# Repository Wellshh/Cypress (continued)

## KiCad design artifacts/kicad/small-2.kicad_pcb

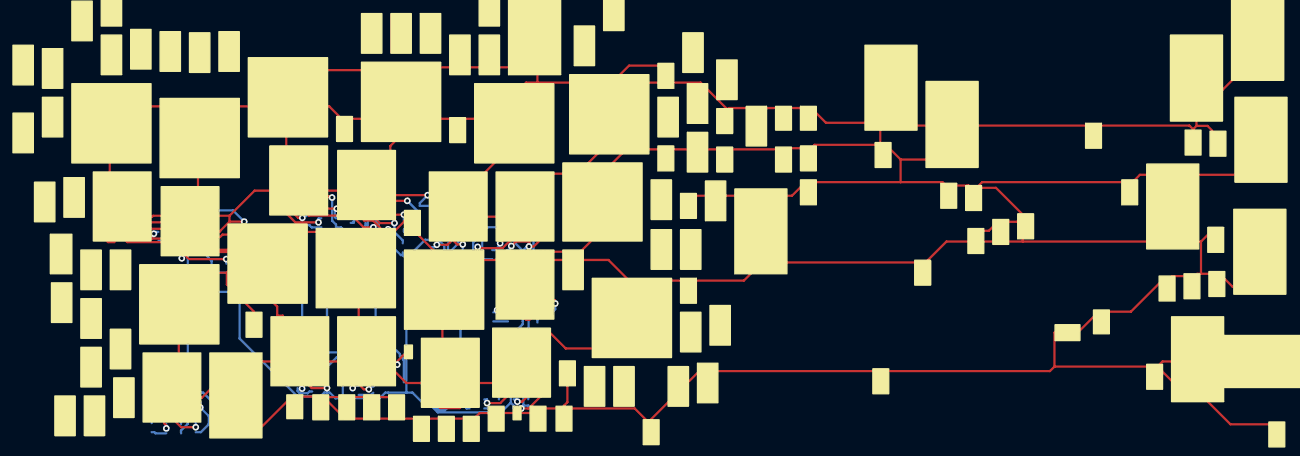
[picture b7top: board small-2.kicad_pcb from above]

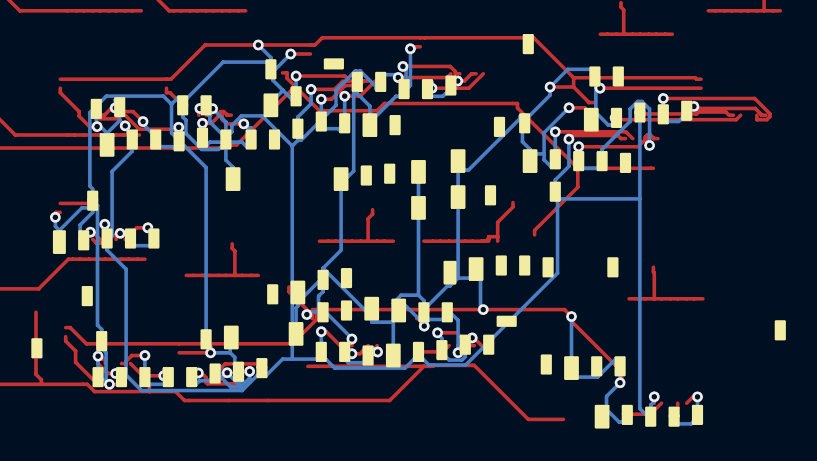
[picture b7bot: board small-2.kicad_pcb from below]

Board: 2 copper layers, 240 parts (106 on the bottom side), 87 nets.

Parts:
C1_1_4: C1_1_4
C1_2_4: C1_2_4
C1_3_4: C1_3_4
C1_4_4: C1_4_4
C1_5_4: C1_5_4
C1_6_4: C1_6_4
C1_7_4: C1_7_4
C1_8_4: C1_8_4
C1_9_4: C1_9_4
C1_10_4: C1_10_4
C1_11_4: C1_11_4
C1_12_4: C1_12_4
C2_1_4: C2_1_4
C2_2_4: C2_2_4
C2_3_4: C2_3_4
C2_4_4: C2_4_4
C2_5_4: C2_5_4
C2_6_4: C2_6_4
C2_7_4: C2_7_4
C2_8_4: C2_8_4
C2_9_4: C2_9_4
C2_10_4: C2_10_4
C2_11_4: C2_11_4
C2_12_4: C2_12_4
C3_1_4: C3_1_4
C3_2_4: C3_2_4
C3_3_4: C3_3_4
C3_4_4: C3_4_4
C3_5_4: C3_5_4
C3_6_4: C3_6_4
C3_7_4: C3_7_4
C3_8_4: C3_8_4
C3_9_4: C3_9_4
C3_10_4: C3_10_4
C3_11_4: C3_11_4
C3_12_4: C3_12_4
C4_1_4: C4_1_4
C4_2_4: C4_2_4
C4_3_4: C4_3_4
C4_4_4: C4_4_4
C4_5_4: C4_5_4
C4_6_4: C4_6_4
C4_7_4: C4_7_4
C4_8_4: C4_8_4
C4_9_4: C4_9_4
C4_10_4: C4_10_4
C4_11_4: C4_11_4
C4_12_4: C4_12_4
C5_1_4: C5_1_4
C5_2_4: C5_2_4
C5_3_4: C5_3_4
C5_4_4: C5_4_4
C5_5_4: C5_5_4
C5_6_4: C5_6_4
C5_7_4: C5_7_4
C5_8_4: C5_8_4
C5_9_4: C5_9_4
C5_10_4: C5_10_4
C5_11_4: C5_11_4
C5_12_4: C5_12_4
C6_1_4: C6_1_4
C6_2_4: C6_2_4
C6_3_4: C6_3_4
C6_4_4: C6_4_4
C6_5_4: C6_5_4
C6_6_4: C6_6_4
C6_7_4: C6_7_4
C6_8_4: C6_8_4
C6_9_4: C6_9_4
C6_10_4: C6_10_4
C6_11_4: C6_11_4
C6_12_4: C6_12_4
C7_1_4: C7_1_4
C7_2_4: C7_2_4
C7_3_4: C7_3_4
C7_4_4: C7_4_4
C7_5_4: C7_5_4
C7_6_4: C7_6_4
C7_7_4: C7_7_4
C7_8_4: C7_8_4
C7_9_4: C7_9_4
C7_10_4: C7_10_4
C7_11_4: C7_11_4
C7_12_4: C7_12_4
C8_1_4: C8_1_4
C8_2_4: C8_2_4
C8_3_4: C8_3_4
C8_4_4: C8_4_4
C8_5_4: C8_5_4
C8_6_4: C8_6_4
C8_7_4: C8_7_4
C8_8_4: C8_8_4
C8_9_4: C8_9_4
C8_10_4: C8_10_4
C8_11_4: C8_11_4
C8_12_4: C8_12_4
C10_1_4: C10_1_4
C10_2_4: C10_2_4
C10_3_4: C10_3_4
C10_4_4: C10_4_4
C10_5_4: C10_5_4
C10_6_4: C10_6_4
C10_7_4: C10_7_4
C10_8_4: C10_8_4
C10_9_4: C10_9_4
C10_10_4: C10_10_4
C10_11_4: C10_11_4
C10_12_4: C10_12_4
C11_1_4: C11_1_4
C11_2_4: C11_2_4
C11_3_4: C11_3_4
C11_4_4: C11_4_4
C11_5_4: C11_5_4
C11_6_4: C11_6_4
C11_7_4: C11_7_4
C11_8_4: C11_8_4
C11_9_4: C11_9_4
C11_10_4: C11_10_4
C11_11_4: C11_11_4
C11_12_4: C11_12_4
C12_1_4: C12_1_4
C12_2_4: C12_2_4
C12_3_4: C12_3_4
C12_4_4: C12_4_4
C12_5_4: C12_5_4
C12_6_4: C12_6_4
C12_7_4: C12_7_4
C12_8_4: C12_8_4
C12_9_4: C12_9_4
C12_10_4: C12_10_4
C12_11_4: C12_11_4
C12_12_4: C12_12_4
C13_1_4: C13_1_4
C13_2_4: C13_2_4
C13_3_4: C13_3_4
C13_4_4: C13_4_4
C13_5_4: C13_5_4
C13_6_4: C13_6_4
C13_7_4: C13_7_4
C13_8_4: C13_8_4
C13_9_4: C13_9_4
C13_10_4: C13_10_4
C13_11_4: C13_11_4
C13_12_4: C13_12_4
C14_1_4: C14_1_4
C14_2_4: C14_2_4
C14_3_4: C14_3_4
C14_4_4: C14_4_4
C14_5_4: C14_5_4
C14_6_4: C14_6_4
C14_7_4: C14_7_4
C14_8_4: C14_8_4
C14_9_4: C14_9_4
C14_10_4: C14_10_4
C14_11_4: C14_11_4
C14_12_4: C14_12_4
C15_1_4: C15_1_4
C15_2_4: C15_2_4
C15_3_4: C15_3_4
C15_4_4: C15_4_4
C15_5_4: C15_5_4
C15_6_4: C15_6_4
C15_7_4: C15_7_4
C15_8_4: C15_8_4
C15_9_4: C15_9_4
C15_10_4: C15_10_4
C15_11_4: C15_11_4
C15_12_4: C15_12_4
L1_1_4: L1_1_4
L1_2_4: L1_2_4
L1_3_4: L1_3_4
L1_4_4: L1_4_4
L1_5_4: L1_5_4
L1_6_4: L1_6_4
L1_7_4: L1_7_4
L1_8_4: L1_8_4
L1_9_4: L1_9_4
L1_10_4: L1_10_4
L1_11_4: L1_11_4
L1_12_4: L1_12_4
R1_1_4: R1_1_4
R1_2_4: R1_2_4
R1_3_4: R1_3_4
R1_4_4: R1_4_4
R1_5_4: R1_5_4
R1_6_4: R1_6_4
R1_7_4: R1_7_4
R1_8_4: R1_8_4
R1_9_4: R1_9_4
R1_10_4: R1_10_4
R1_11_4: R1_11_4
R1_12_4: R1_12_4
R2_1_4: R2_1_4
R2_2_4: R2_2_4
R2_3_4: R2_3_4
R2_4_4: R2_4_4
R2_5_4: R2_5_4
R2_6_4: R2_6_4
R2_7_4: R2_7_4
R2_8_4: R2_8_4
R2_9_4: R2_9_4
R2_10_4: R2_10_4
R2_11_4: R2_11_4
R2_12_4: R2_12_4
R3_1_4: R3_1_4
R3_2_4: R3_2_4
R3_3_4: R3_3_4
R3_4_4: R3_4_4
R3_5_4: R3_5_4
R3_6_4: R3_6_4
R3_7_4: R3_7_4
R3_8_4: R3_8_4
R3_9_4: R3_9_4
R3_10_4: R3_10_4
R3_11_4: R3_11_4
R3_12_4: R3_12_4
R4_1_4: R4_1_4
R4_2_4: R4_2_4
R4_3_4: R4_3_4
R4_4_4: R4_4_4
R4_5_4: R4_5_4
R4_6_4: R4_6_4
R4_7_4: R4_7_4
R4_8_4: R4_8_4
R4_9_4: R4_9_4
R4_10_4: R4_10_4
R4_11_4: R4_11_4
R4_12_4: R4_12_4
U1_1_4: U1_1_4
U1_2_4: U1_2_4
U1_3_4: U1_3_4
U1_4_4: U1_4_4
U1_5_4: U1_5_4
U1_6_4: U1_6_4
U1_7_4: U1_7_4
U1_8_4: U1_8_4
U1_9_4: U1_9_4
U1_10_4: U1_10_4
U1_11_4: U1_11_4
U1_12_4: U1_12_4

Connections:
AG_PH_BOOTRC_24: C11_1_4.0, R4_1_4.0
AG_PH_BOOTRC_25: C11_2_4.0, R4_2_4.0
AG_PH_BOOTRC_26: C11_3_4.0, R4_3_4.0
AG_PH_BOOTRC_27: C11_4_4.0, R4_4_4.0
AG_PH_BOOTRC_28: C11_5_4.0, R4_5_4.0
AG_PH_BOOTRC_29: C11_6_4.0, R4_6_4.0
AG_PH_BOOTRC_30: C11_7_4.0, R4_7_4.0
AG_PH_BOOTRC_31: C11_8_4.0, R4_8_4.0
AG_PH_BOOTRC_32: C11_9_4.0, R4_9_4.0
AG_PH_BOOTRC_33: C11_11_4.0, R4_11_4.0
AG_PH_BOOTRC_34: C11_10_4.0, R4_10_4.0
AG_PH_BOOTRC_35: C11_12_4.0, R4_12_4.0
AG_PH_BOOT_24: R4_1_4.1, U1_1_4.2
AG_PH_BOOT_25: R4_2_4.1, U1_2_4.2
AG_PH_BOOT_26: R4_3_4.1, U1_3_4.2
AG_PH_BOOT_27: R4_4_4.1, U1_4_4.2
AG_PH_BOOT_28: R4_5_4.1, U1_5_4.2
AG_PH_BOOT_29: R4_6_4.1, U1_6_4.2
AG_PH_BOOT_30: R4_7_4.1, U1_7_4.2
AG_PH_BOOT_31: R4_8_4.1, U1_8_4.2
AG_PH_BOOT_32: R4_9_4.1, U1_9_4.2
AG_PH_BOOT_33: R4_11_4.1, U1_11_4.2
AG_PH_BOOT_34: R4_10_4.1, U1_10_4.2
AG_PH_BOOT_35: R4_12_4.1, U1_12_4.2
AG_PH_PHASE_24: C11_1_4.1, U1_1_4.3
AG_PH_PHASE_25: C11_2_4.1, U1_2_4.3
AG_PH_PHASE_26: C11_3_4.1, U1_3_4.3
AG_PH_PHASE_27: C11_4_4.1, U1_4_4.3
AG_PH_PHASE_28: C11_5_4.1, U1_5_4.3
AG_PH_PHASE_29: C11_6_4.1, U1_6_4.3
AG_PH_PHASE_30: C11_7_4.1, U1_7_4.3
AG_PH_PHASE_31: C11_8_4.1, U1_8_4.3
AG_PH_PHASE_32: C11_9_4.1, U1_9_4.3
AG_PH_PHASE_33: C11_11_4.1, U1_11_4.3
AG_PH_PHASE_34: C11_10_4.1, U1_10_4.3
AG_PH_PHASE_35: C11_12_4.1, U1_12_4.3
AG_PH_SW_24: L1_1_4.0, U1_1_4.4, U1_1_4.5, U1_1_4.6, U1_1_4.7, U1_1_4.8, U1_1_4.9, U1_1_4.10, U1_1_4.11, U1_1_4.12, U1_1_4.13
AG_PH_SW_25: L1_2_4.0, U1_2_4.4, U1_2_4.5, U1_2_4.6, U1_2_4.7, U1_2_4.8, U1_2_4.9, U1_2_4.10, U1_2_4.11, U1_2_4.12, U1_2_4.13
AG_PH_SW_26: L1_3_4.0, U1_3_4.4, U1_3_4.5, U1_3_4.6, U1_3_4.7, U1_3_4.8, U1_3_4.9, U1_3_4.10, U1_3_4.11, U1_3_4.12, U1_3_4.13
AG_PH_SW_27: L1_4_4.0, U1_4_4.4, U1_4_4.5, U1_4_4.6, U1_4_4.7, U1_4_4.8, U1_4_4.9, U1_4_4.10, U1_4_4.11, U1_4_4.12, U1_4_4.13
AG_PH_SW_28: L1_5_4.0, U1_5_4.4, U1_5_4.5, U1_5_4.6, U1_5_4.7, U1_5_4.8, U1_5_4.9, U1_5_4.10, U1_5_4.11, U1_5_4.12, U1_5_4.13
AG_PH_SW_29: L1_6_4.0, U1_6_4.4, U1_6_4.5, U1_6_4.6, U1_6_4.7, U1_6_4.8, U1_6_4.9, U1_6_4.10, U1_6_4.11, U1_6_4.12, U1_6_4.13
AG_PH_SW_30: L1_7_4.0, U1_7_4.4, U1_7_4.5, U1_7_4.6, U1_7_4.7, U1_7_4.8, U1_7_4.9, U1_7_4.10, U1_7_4.11, U1_7_4.12, U1_7_4.13
AG_PH_SW_31: L1_8_4.0, U1_8_4.4, U1_8_4.5, U1_8_4.6, U1_8_4.7, U1_8_4.8, U1_8_4.9, U1_8_4.10, U1_8_4.11, U1_8_4.12, U1_8_4.13
AG_PH_SW_32: L1_9_4.0, U1_9_4.4, U1_9_4.5, U1_9_4.6, U1_9_4.7, U1_9_4.8, U1_9_4.9, U1_9_4.10, U1_9_4.11, U1_9_4.12, U1_9_4.13
AG_PH_SW_33: L1_11_4.0, U1_11_4.4, U1_11_4.5, U1_11_4.6, U1_11_4.7, U1_11_4.8, U1_11_4.9, U1_11_4.10, U1_11_4.11, U1_11_4.12, U1_11_4.13
AG_PH_SW_34: L1_10_4.0, U1_10_4.4, U1_10_4.5, U1_10_4.6, U1_10_4.7, U1_10_4.8, U1_10_4.9, U1_10_4.10, U1_10_4.11, U1_10_4.12, U1_10_4.13
AG_PH_SW_35: L1_12_4.0, U1_12_4.4, U1_12_4.5, U1_12_4.6, U1_12_4.7, U1_12_4.8, U1_12_4.9, U1_12_4.10, U1_12_4.11, U1_12_4.12, U1_12_4.13
S_PH_EN_24: R3_1_4.0, U1_1_4.21
S_PH_EN_25: R3_2_4.0, U1_2_4.21
S_PH_EN_26: R3_3_4.0, U1_3_4.21
S_PH_EN_27: R3_4_4.0, U1_4_4.21
S_PH_EN_28: R3_5_4.0, U1_5_4.21
S_PH_EN_29: R3_6_4.0, U1_6_4.21
S_PH_EN_30: R3_7_4.0, U1_7_4.21
S_PH_EN_31: R3_8_4.0, U1_8_4.21
S_PH_EN_32: R3_9_4.0, U1_9_4.21
S_PH_EN_33: R3_11_4.0, U1_11_4.21
S_PH_EN_34: R3_10_4.0, U1_10_4.21
S_PH_EN_35: R3_12_4.0, U1_12_4.21
S_PH_TAO_24: R2_1_4.0, U1_1_4.22
S_PH_TAO_25: R2_2_4.0, U1_2_4.22
S_PH_TAO_26: R2_3_4.0, U1_3_4.22
S_PH_TAO_27: R2_4_4.0, U1_4_4.22
S_PH_TAO_28: R2_5_4.0, U1_5_4.22
S_PH_TAO_29: R2_6_4.0, U1_6_4.22
S_PH_TAO_30: R2_7_4.0, U1_7_4.22
S_PH_TAO_31: R2_8_4.0, U1_8_4.22
S_PH_TAO_32: R2_9_4.0, U1_9_4.22
S_PH_TAO_33: R2_11_4.0, U1_11_4.22
S_PH_TAO_34: R2_10_4.0, U1_10_4.22
S_PH_TAO_35: R2_12_4.0, U1_12_4.22
S_PH_VCC_24: C7_1_4.0, R1_1_4.0, R3_1_4.1, U1_1_4.23
S_PH_VCC_25: C7_2_4.0, R1_2_4.0, R3_2_4.1, U1_2_4.23
S_PH_VCC_26: C7_3_4.0, R1_3_4.0, R3_3_4.1, U1_3_4.23
S_PH_VCC_27: C7_4_4.0, R1_4_4.0, R3_4_4.1, U1_4_4.23
S_PH_VCC_28: C7_5_4.0, R1_5_4.0, R3_5_4.1, U1_5_4.23
S_PH_VCC_29: C7_6_4.0, R1_6_4.0, R3_6_4.1, U1_6_4.23
S_PH_VCC_30: C7_7_4.0, R1_7_4.0, R3_7_4.1, U1_7_4.23
S_PH_VCC_31: C7_8_4.0, R1_8_4.0, R3_8_4.1, U1_8_4.23
S_PH_VCC_32: C7_9_4.0, R1_9_4.0, R3_9_4.1, U1_9_4.23
S_PH_VCC_33: C7_11_4.0, R1_11_4.0, R3_11_4.1, U1_11_4.23
S_PH_VCC_34: C7_10_4.0, R1_10_4.0, R3_10_4.1, U1_10_4.23
S_PH_VCC_35: C7_12_4.0, R1_12_4.0, R3_12_4.1, U1_12_4.23
S_VDD_TAO_4: R2_1_4.1, R2_2_4.1, R2_3_4.1, R2_4_4.1, R2_5_4.1, R2_6_4.1, R2_7_4.1, R2_8_4.1, R2_9_4.1, R2_10_4.1, R2_11_4.1, R2_12_4.1
VDD_2: C10_1_4.0, C10_2_4.0, C10_3_4.0, C10_4_4.0, C10_5_4.0, C10_6_4.0, C10_7_4.0, C10_8_4.0, C10_9_4.0, C10_10_4.0, C10_11_4.0, C10_12_4.0, C12_1_4.0, C12_2_4.0, C12_3_4.0, C12_4_4.0, C12_5_4.0, C12_6_4.0, C12_7_4.0, C12_8_4.0, C12_9_4.0, C12_10_4.0, C12_11_4.0, C12_12_4.0, C13_1_4.0, C13_2_4.0, C13_3_4.0, C13_4_4.0, C13_5_4.0, C13_6_4.0, C13_7_4.0, C13_8_4.0, C13_9_4.0, C13_10_4.0, C13_11_4.0, C13_12_4.0, C14_1_4.0, C14_2_4.0, C14_3_4.0, C14_4_4.0, C14_5_4.0, C14_6_4.0, C14_7_4.0, C14_8_4.0, C14_9_4.0, C14_10_4.0, C14_11_4.0, C14_12_4.0, C15_1_4.0, C15_2_4.0, C15_3_4.0, C15_4_4.0, C15_5_4.0, C15_6_4.0, C15_7_4.0, C15_8_4.0, C15_9_4.0, C15_10_4.0, C15_11_4.0, C15_12_4.0, L1_1_4.1, L1_2_4.1, L1_3_4.1, L1_4_4.1, L1_5_4.1, L1_6_4.1, L1_7_4.1, L1_8_4.1, L1_9_4.1, L1_10_4.1, L1_11_4.1, L1_12_4.1
VDRV: C5_1_4.0, C5_2_4.0, C5_3_4.0, C5_4_4.0, C5_5_4.0, C5_6_4.0, C5_7_4.0, C5_8_4.0, C5_9_4.0, C5_10_4.0, C5_11_4.0, C5_12_4.0, R1_1_4.1, R1_2_4.1, R1_3_4.1, R1_4_4.1, R1_5_4.1, R1_6_4.1, R1_7_4.1, R1_8_4.1, R1_9_4.1, R1_10_4.1, R1_11_4.1, R1_12_4.1, U1_1_4.25, U1_2_4.25, U1_3_4.25, U1_4_4.25, U1_5_4.25, U1_6_4.25, U1_7_4.25, U1_8_4.25, U1_9_4.25, U1_10_4.25, U1_11_4.25, U1_12_4.25

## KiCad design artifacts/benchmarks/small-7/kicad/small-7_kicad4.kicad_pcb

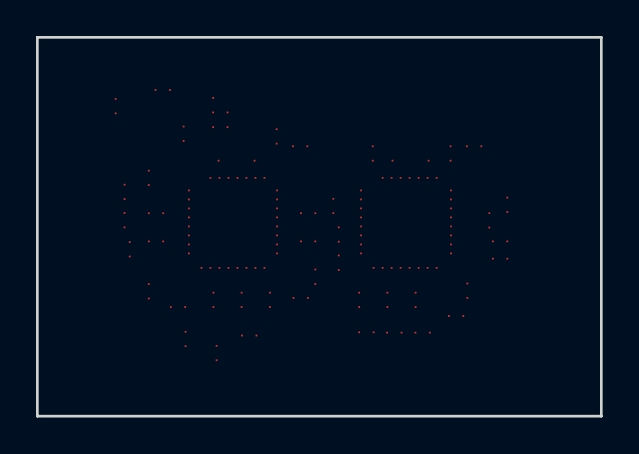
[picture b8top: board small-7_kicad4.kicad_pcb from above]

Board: 2 copper layers, 31.3 x 21.0 mm, 50 parts (0 on the bottom side), 44 nets, no tracks yet.

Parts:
C0: C0; 115-3253-000
C1: C1; 115-3253-000
C2: C2; 195-0128-000
C3: C3; 032-0863-000
C4: C4; 032-0863-000
C5: C5; 195-0128-000
C6: C6; 195-0128-000
C7: C7; 195-0128-000
C8: C8; 195-0128-000
C9: C9; 195-0128-000
C10: C10; 195-0128-000
C11: C11; 195-0005-000
C12: C12; 195-0005-000
C13: C13; 195-0128-000
C14: C14; 195-0128-000
C15: C15; 195-0128-000
C16: C16; 195-0003-000
C17: C17; 195-2655-000
C18: C18; 195-0128-000
C19: C19; 195-0128-000
C20: C20; 195-0128-000
C21: C21; 195-0128-000
C22: C22; 195-0128-000
C23: C23; 195-0128-000
C24: C24; 195-0128-000
C25: C25; 195-0128-000
C26: C26; 195-0128-000
C27: C27; 195-0128-000
C28: C28; 195-0128-000
C29: C29; 032-0863-000
C30: C30; 195-0128-000
C31: C31; 195-0128-000
C32: C32; 195-0128-000
C33: C33; 195-0128-000
C34: C34; 195-0128-000
C35: C35; 032-0863-000
C36: C36; 195-0128-000
C37: C37; 195-0128-000
C38: C38; 195-0128-000
C39: C39; 195-0128-000
C40: C40; 195-0128-000
C41: C41; 195-0128-000
C42: C42; 195-0128-000
C43: C43; 195-0128-000
C44: C44; 195-0128-000
C45: C45; 195-0128-000
C46: C46; 195-0128-000
C47: C47; 195-3953-000
C48: C48; 195-0128-000
C49: C49; 195-3953-000

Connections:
NET_45: C0.27, C0.31, C1.27, C1.31, C3.1, C4.1, C11.2, C12.2, C16.1, C29.1, C35.1, C49.2
NET_73: C1.26, C47.2
NET_74: C0.26, C49.1
NET_431: C1.21, C6.1
NET_452: C1.22, C7.1
NET_456: C0.1, C5.1
NET_501: C0.28, C1.28, C16.2, C17.2
NET_526: C0.2, C48.1
NET_528: C0.3, C46.1
NET_536: C0.4, C25.1
NET_538: C0.5, C20.1
NET_1836: C0.29, C1.29, C12.1
NET_1837: C0.30, C1.30, C11.1
NET_4122: C1.15, C15.1
NET_4129: C0.6, C2.1
NET_4139: C1.12, C31.1
NET_4163: C1.11, C34.1
NET_4172: C1.19, C36.1
NET_4179: C1.20, C32.1
NET_4187: C1.13, C30.1
NET_4196: C1.14, C24.1
NET_4213: C1.24, C10.1
NET_4215: C0.16, C9.1
NET_4231: C1.23, C43.1
NET_4233: C0.15, C8.1
NET_4244: C0.13, C45.2
NET_4247: C0.9, C42.1
NET_4250: C0.11, C33.1
NET_4258: C0.14, C44.2
NET_4261: C0.10, C41.1
NET_4264: C0.12, C39.1
NET_4303: C1.4, C18.1
NET_4308: C1.9, C27.1
NET_4313: C1.5, C23.1
NET_4318: C1.10, C26.1
NET_4383: C1.2, C13.1
NET_4388: C1.7, C21.1
NET_4393: C1.3, C19.1
NET_4398: C1.8, C28.1
NET_4427: C1.16, C40.1
NET_4586: C1.1, C14.1
NET_4591: C1.6, C22.1
NET_4651: C1.17, C38.1
NET_4660: C1.18, C37.1

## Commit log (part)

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2026-03-03 Add artifacts
